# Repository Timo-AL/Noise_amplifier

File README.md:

# here are some problem to fix！
1000x and 100x amplifier for power supplier noise measurement

the miniest noise voltage which this amplifier can measure is 6uVrms(0.1Hz~200KHz BW)

Just install like ibom, and enjoy

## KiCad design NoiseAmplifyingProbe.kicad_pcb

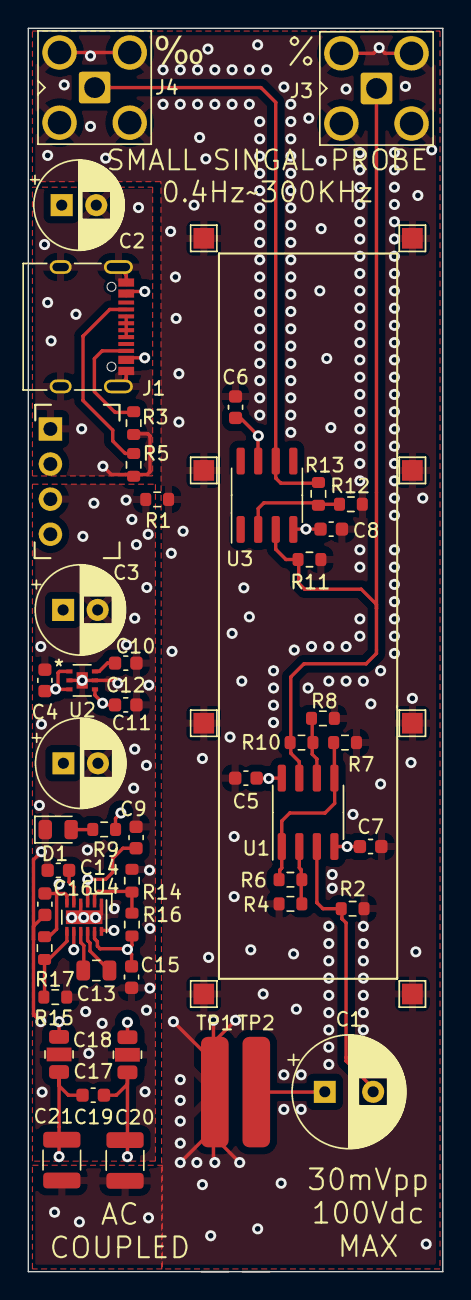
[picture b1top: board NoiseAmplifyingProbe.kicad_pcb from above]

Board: 4 copper layers, 30.0 x 90.0 mm, 57 parts (0 on the bottom side), 28 nets.

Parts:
C1: 10uf; CP_Radial_D8.0mm_P3.50mm
C2, C3, C11: 220uf; CP_Radial_D6.3mm_P2.50mm
C4, C5, C6, C7, C8, C10: 100nf; C_0603_1608Metric
C9: 100nF; C_0603_1608Metric
C12: 1uf; C_0603_1608Metric
C13: 4.7uF; C_0805_2012Metric
C14, C15, C16, C19: 2.2uF; C_0603_1608Metric
C17, C18: 104; C_Feed_0805_2012Metric
C20, C21: 100uf; C_1210_3225Metric
D1: LED; LED_0805_2012Metric
J1: USB_C_Receptacle_USB2.0; USB_C_Receptacle_XKB_U262-16XN-4BVC11
J2: Conn_01x04; 5V1W
J3, J4: BNC; SMA_Amphenol_901-143_Horizontal
R1: 0; R_0603_1608Metric
R2: 200k; R_0603_1608Metric
R3, R5: 5.1k; R_0603_1608Metric
R4, R8, R12: 2.1k; R_0603_1608Metric
R6, R10, R13: 18.7k; R_0603_1608Metric
R7, R11: 51k; R_0603_1608Metric
R9: 200; R_0603_1608Metric
R14, R15: 51K; R_0603_1608Metric
R16: 78.7k; R_0603_1608Metric
R17: 75K; R_0603_1608Metric
TP1, TP2: TestPoint; P50 Tip
TP3, TP4, TP5, TP6, TP7, TP8, TP9, TP10: RF_Shell; TestPoint_Pad_1.5x1.5mm
U1: ADA4522-2; SOIC-8_3.9x4.9mm_P1.27mm
U2: NCV8570BMN300R2G
U3: LME49710; SOIC-8_3.9x4.9mm_P1.27mm
U4: LM27762; WSON-12-1EP_3x2mm_P0.5mm_EP1x2.65_ThermalVias

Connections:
+5V: C3.1, C4.1, J2.4, U2.1 (EN), U2.3 (IN)
GND: C3.2, C4.2, C9.2, C10.2, C11.2, C12.2, C14.2, C15.1, C16.2, C17.2, C18.2, D1.1 (K), J2.3, R1.1, R14.2, R15.2, U2.2 (GND), U2.5 (GND), U2.7 (EPAD), U4.1 (PGOOD), U4.4 (GND), U4.13 (PAD)
GNDA: C5.2, C6.2, C7.2, C8.2, C20.2, C21.1, J3.2 (Ext), J4.2 (Ext), R1.2, R2.2, R4.1, R7.2, R8.1, R11.2, R12.1, TP1.1, TP3.1, TP4.1, TP5.1, TP6.1, TP7.1, TP8.1, TP9.1, TP10.1
GNDPWR: C2.2, J1.A1 (GND), J1.A12 (GND), J1.B1 (GND), J1.B12 (GND), J1.S1 (SHIELD), J2.1, R3.1, R5.1
unnamed: C1.1, TP2.1
unnamed: D1.2 (A), R9.1
unnamed: J1.A5 (CC1), R5.2
unnamed: J1.B5 (CC2), R3.2
unnamed: J1.A6 (D+), J1.A7 (D-), J1.B6 (D+), J1.B7 (D-)
unnamed: C2.1, J1.A4 (VBUS), J1.A9 (VBUS), J1.B4 (VBUS), J1.B9 (VBUS), J2.2
unnamed: J3.1 (In), R10.2, R11.1, U1.7, U3.3 (+)
unnamed: J4.1 (In), R13.2, U3.6
unnamed: C1.2, R2.1, U1.3 (+)
unnamed: R6.2, R7.1, U1.1, U1.5 (+)
unnamed: R4.2, R6.1, U1.2 (-)
unnamed: R8.2, R10.1, U1.6 (-)
unnamed: C10.1, U2.6 (BYP)
unnamed: R12.2, R13.1, U3.2 (-)
unnamed: C13.1, U4.10 (C+)
unnamed: C13.2, U4.9 (C-)
unnamed: C14.1, U4.5 (CP)
unnamed: R14.1, R16.2, U4.2 (FB+)
unnamed: R15.1, R17.2, U4.7 (FB-)
unnamed: C15.2, C17.1, R16.1, U4.11 (OUT+)
unnamed: C16.1, C18.3, R17.1, U4.6 (OUT-)
VAA: C5.1, C6.1, C17.3, C19.1, C20.1, U1.8 (V+), U3.7 (V+)
VCC: C9.1, C11.1, C12.1, R9.2, U2.4 (OUT), U4.3 (VIN), U4.8 (EN-), U4.12 (EN+)
VEE: C7.1, C8.1, C18.1, C19.2, C21.2, U1.4 (V-), U3.4 (V-)

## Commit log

2022-09-17 upload

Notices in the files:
parts and their libraries:
Copyright 2021 Accelerated Designs. All rights reserved.
